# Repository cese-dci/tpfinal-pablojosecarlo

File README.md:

# tpfinal-pablojosecarlo

DCI CESE 10º Cohorte 2020 Pablo José Carlos Alonso Castillo

Escaner de Campos Magnéticos Superficiales (ECMag)

Descripción del dispositivo:

El objeto del scanner  es relevar los campos magnéticos a distancias de 1 a 3 mm de las superficies, correlacionando la posición de sensores magnéticos con la de un encoder absoluto y comunicar los resultados a una PC via cable USB, RS232 o por medios inalámbricos 
 
Para ese fin se implementa un circuito dividido en dos secciones con los uP ATM328 y PIC18F2550

El ATM328 se encarga de la adquisición de señales del encoder alsoluto de 12 bits, de los sensores magnéticos y de la interfaz de usuario a través de un display i2c, un buzzer y dos pulsadores.

El PIC18F2550 se encarga de las comunicaciones USB, seriales e inalámbricas y de servir de buffer de datos.

los uP cuentan con pulsadores de reseteo.

Puesto que el encoder funciona con 12V se ha dispuesto también de un convertidor DC-DC de 5V a 12V

La alimentación puede ser desde el puerto USB o con fuente externa de 5V

La salida a display i2c muestra las lecturas instantáneas de los campos magnéticos y la posición del encoder; buzzer de fuera de rango y dos pulsadores de seteo y nueva medición.

Pablo J.C. Alonso Castillo

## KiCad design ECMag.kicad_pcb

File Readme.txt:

Escáner Magnético de Soldaduras:

El objeto del scanner  es relevar los campos magnéticos a distancias de 1 a 3 mm de las superficies, correlacionando la posición de sensores magnéticos con la de un encoder absoluto y comunicar los resultados a una PC via cable USB, RS232 o por medios inalámbricos 
 
Para ese fin se implementa un circuito dividido en dos secciones con los uP ATM328 y PIC18F2550

El ATM328 se encarga de la adquisición de señales del encoder alsoluto de 12 bits y de los sensores magnéticos. también de la interfaz de usuario a través de un display i2c, un buzzer y dos pulsadores

El PIC18F2550 se encarga de las comunicaciones USB, seriales e inalámbricas y de servir de buffer de datos

los uP cuentan con pulsadores de reseteo.

Puesto que el encoder funciona con 12V se ha dispuesto también de un convertidor DC-DC de 5V a 12V

La salida a display i2c muestra las lecturas instantáneas de los campos magnéticos y la posición del encoder; buzzer de fuera de rango y dos pulsadores de seteo y nueva medición.

Pablo J.C. Alonso Castillo

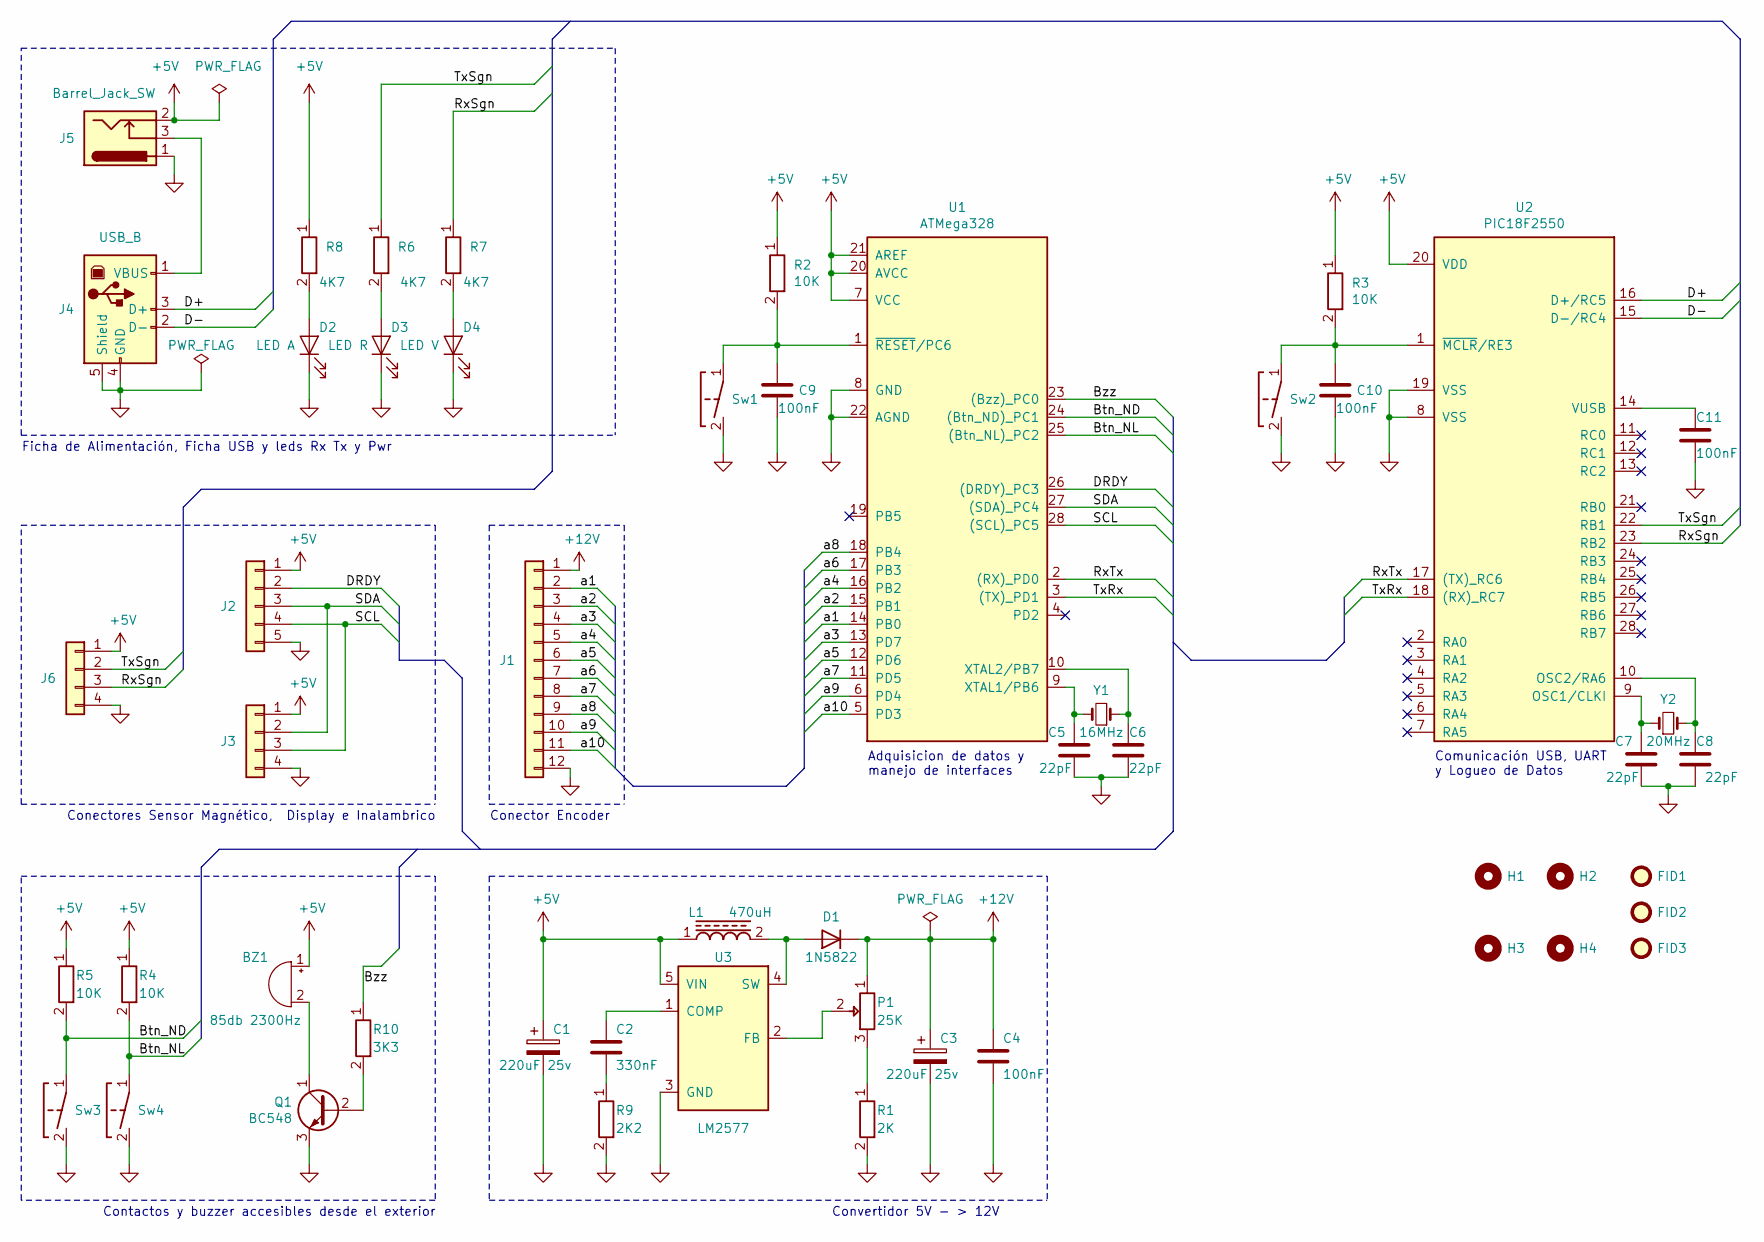
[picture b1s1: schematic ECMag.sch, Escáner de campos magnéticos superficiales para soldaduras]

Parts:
BZ1: 85db 2300Hz; Buzzer_12x9.5RM7.6; Digikey 102-1458-ND
C1, C3: 220uF 25v; CP_Radial_D8.0mm_P5.00mm
C2: 330nF; C_Disc_D5.1mm_W3.2mm_P5.00mm
C4, C9, C10, C11: 100nF; C_Disc_D5.1mm_W3.2mm_P5.00mm
C5, C6, C7, C8: 22pF; C_Disc_D6.0mm_W2.5mm_P5.00mm
D1: 1N5822; D_A-405_P10.16mm_Horizontal; Digikey 497-11370-1-ND
D2: LED A; LED_D3.0mm
D3: LED R; LED_D3.0mm
D4: LED V; LED_D3.0mm
FID1, FID2, FID3: Fiducial; Fiducial_1mm_Mask2mm
H1, H2, H3, H4: MountingHole; MountingHole_3.2mm_M3
J1: Conn_01x12; PinHeader_1x12_P2.54mm_Vertical; Digikey 952-3302-ND
J2: Conn_01x05; PinHeader_1x05_P2.54mm_Vertical; Digikey 952-3302-ND
J3, J6: Conn_01x04; PinHeader_1x04_P2.54mm_Vertical; Digikey 952-3302-ND
J4: USB_B; USB_B_OST_USB-B1HSxx_Horizontal; Digikey WM12785-ND
J5: Barrel_Jack_SW; BarrelJack_Wuerth_6941xx301002; Digikey CP-202A-ND
L1: 470uH; L_Radial_D7.5mm_P5.00mm_Fastron_07P; Digikey 445-174743-2-ND
P1: 25K; Potentiometer_Bourns_3266W_Vertical
Q1: BC548; TO-92_Inline; Digikey BC548-ND
R1: 2K; R_Axial_DIN0207_L6.3mm_D2.5mm_P7.62mm_Horizontal
R2, R3, R4, R5: 10K; R_Axial_DIN0207_L6.3mm_D2.5mm_P7.62mm_Horizontal
R6, R7, R8: 4K7; R_Axial_DIN0207_L6.3mm_D2.5mm_P7.62mm_Horizontal
R9: 2K2; R_Axial_DIN0207_L6.3mm_D2.5mm_P7.62mm_Horizontal
R10: 3K3; R_Axial_DIN0207_L6.3mm_D2.5mm_P7.62mm_Horizontal
Sw1, Sw2, Sw3, Sw4: Tactil Switch B3F NA; SW_PUSH_6mm_H5mm; Digikey B3F-1060
U1: ATMega328; DIP-28_W7.62mm; Digikey ATMEGA328-PU-ND
U2: PIC18F2550; DIP-28_W7.62mm; Digikey PIC18F2550-I/SP-ND
U3: LM2577; TO-220-5_P3.4x3.7mm_StaggerOdd_Lead3.8mm_Vertical; Digikey LM2577SX-ADJ/NOPBTR-ND
Y1: 16MHz; Crystal_HC49-U_Vertical; Digikey 1923-1788-ND
Y2: 20MHz; Crystal_HC49-U_Vertical; Digikey 1923-1441-ND

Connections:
+5V: BZ1.1 (-), C1.1, J2.1, J3.1, J5.2, J6.1, L1.1, R2.1, R3.1, R4.1, R5.1, R8.1, U1.7 (VCC), U1.20 (AVCC), U1.21 (AREF), U2.20 (VDD), U3.5 (VIN)
+12V: C3.1, C4.1, D1.2 (K), J1.1, P1.1
/Btn_ND: R5.2, Sw3.1, U1.24 ((Btn_ND)_PC1)
/Btn_NL: R4.2, Sw4.1, U1.25 ((Btn_NL)_PC2)
/Bzz: R10.1, U1.23 ((Bzz)_PC0)
/D+: J4.3 (D+), U2.16 (D+/RC5)
/D-: J4.2 (D-), U2.15 (D-/RC4)
/DRDY: J2.2, U1.26 ((DRDY)_PC3)
/RxSgn: J6.3, R7.1, U2.23 (RB2)
/RxTx: U1.2 ((RX)_PD0), U2.17 ((TX)_RC6)
/SCL: J2.4, J3.3, U1.28 ((SCL)_PC5)
/SDA: J2.3, J3.2, U1.27 ((SDA)_PC4)
/TxRx: U1.3 ((TX)_PD1), U2.18 ((RX)_RC7)
/TxSgn: J6.2, R6.1, U2.22 (RB1)
/a1: J1.2, U1.14 (PB0)
/a2: J1.3, U1.15 (PB1)
/a3: J1.4, U1.13 (PD7)
/a4: J1.5, U1.16 (PB2)
/a5: J1.6, U1.12 (PD6)
/a6: J1.7, U1.17 (PB3)
/a7: J1.8, U1.11 (PD5)
/a8: J1.9, U1.18 (PB4)
/a9: J1.10, U1.6 (PD4)
/a10: J1.11, U1.5 (PD3)
GND: C1.2, C3.2, C4.2, C5.2, C6.2, C7.2, C8.2, C9.2, C10.2, C11.2, D2.1 (K), D3.1 (K), D4.1 (K), J1.12, J2.5, J3.4, J4.4 (GND), J4.5 (Shield), J5.1, J6.4, Q1.3 (E), R1.2, R9.2, Sw1.2, Sw2.2, Sw3.2, Sw4.2, U1.8 (GND), U1.22 (AGND), U2.8 (VSS), U2.19 (VSS), U3.3 (GND)
unnamed: BZ1.2 (+), Q1.1 (C)
unnamed: C2.1, U3.1 (COMP)
unnamed: C2.2, R9.1
unnamed: C5.1, U1.9 (XTAL1/PB6), Y1.2
unnamed: C6.1, U1.10 (XTAL2/PB7), Y1.1
unnamed: C7.1, U2.9 (OSC1/CLKI), Y2.1
unnamed: C8.1, U2.10 (OSC2/RA6), Y2.2
unnamed: C9.1, R2.2, Sw1.1, U1.1 (~RESET~/PC6)
unnamed: C10.1, R3.2, Sw2.1, U2.1 (~MCLR~/RE3)
unnamed: C11.1, U2.14 (VUSB)
unnamed: D1.1 (A), L1.2, U3.4 (SW)
unnamed: D2.2 (A), R8.2
unnamed: D3.2 (A), R6.2
unnamed: D4.2 (A), R7.2
unnamed: J4.1 (VBUS), J5.3
unnamed: P1.2, U3.2 (FB)
unnamed: P1.3, R1.1
unnamed: Q1.2 (B), R10.2

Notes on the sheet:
Convertidor 5V - > 12V
Conector Encoder
Contactos y buzzer accesibles desde el exterior
Conectores Sensor Magnético, Display e Inalambrico
Ficha de Alimentación, Ficha USB y leds Rx Tx y Pwr
Comunicación USB, UART y Logueo de Datos
Adquisicion de datos y manejo de interfaces

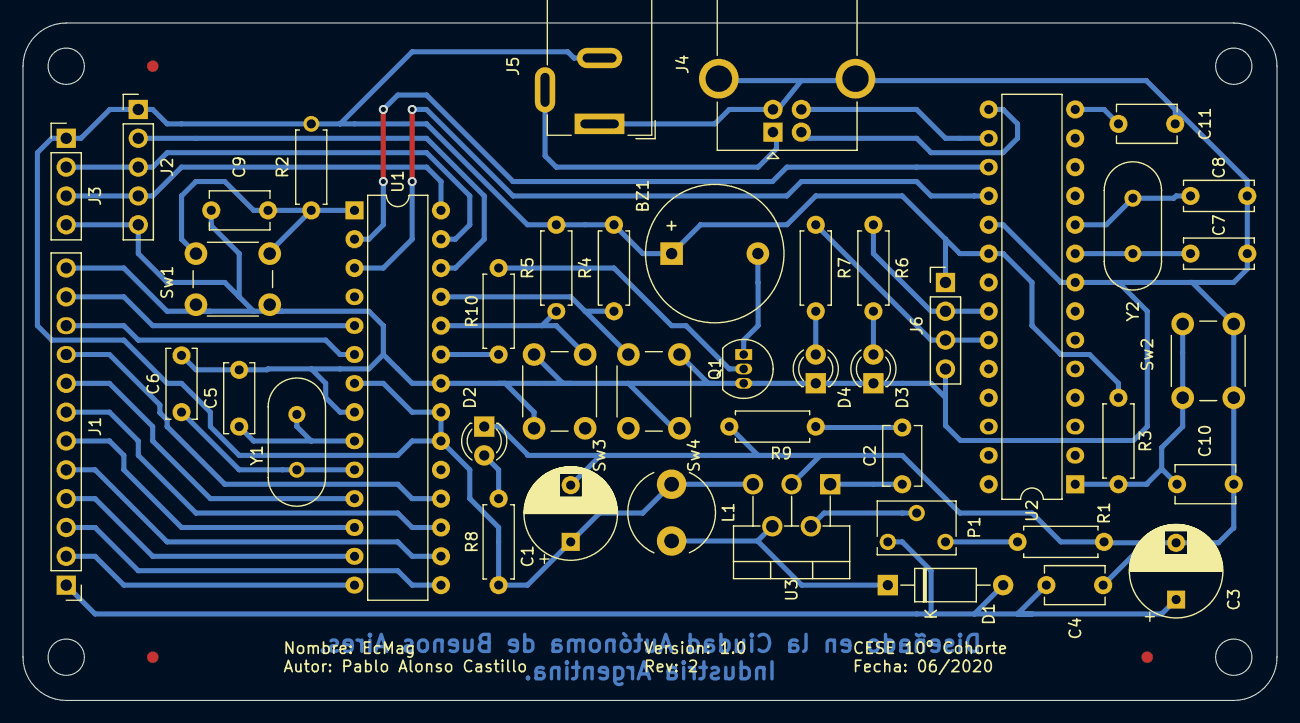
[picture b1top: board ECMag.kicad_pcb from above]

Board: 2 copper layers, 110.5 x 59.7 mm, 51 parts (0 on the bottom side), 43 nets.

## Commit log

2020-05-13 Primer commit
2020-05-30 Commit de lo hecho hasta el 30 de mayo de 2020
2020-06-05 Esquemáticounifilar terminado. Faltan footprints y datasheets
2020-06-05 Esquemático terminado, con footprints y datasheets
2020-06-05 Actualizacion de datasheets
2020-06-06 Rediseño de fuente step up 5v-12v y Actualizacion de datasheets
2020-06-07 compleción de huellas faltantes y reemplazo de etiquetas por buses
2020-06-07 Inicio de PCB
2020-06-10 agregado de valores de los componentes en el esquemático
2020-06-11 Edicion de huella de pulsadores y primer pcb
2020-06-12 Correcciones faltantes indicadas por el profesor
2020-06-13 Correcciones faltantes indicadas por el profesor - detalles
2020-06-19 primera versión del pcb
2020-06-20 cambio de huellas del pulsador
2020-06-25 Arreglo de F.Silks y F.Fab
2020-06-25 Paso de los tracks de 0.25 a 0.45, tracks de senhales y potencia
2020-06-26 Planos de Tierra de Fuente Switchin de 12V y Plano General
2020-07-03 Agregadas las imagenes 3D del power jack y del USB B, corregidas esquinas del pcb, agregados fiduciarios, parametros del circuito, grilla, datos del fabricante, dimensiones del pcb, datos de serigraf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
2020-07-03 error de salvado
2020-07-03 Correcciones en los comentarios de la capa Dwgs
2020-07-03 Eliminación de Tracks superfluos tapados por otros tracks
2020-07-17 1.- Reemplaxado K por Sw en el esquemático.
2020-07-17 Arreglos finales sugeridos por el profesor. Ver archivo: notas al profesor
